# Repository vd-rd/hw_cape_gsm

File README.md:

## Description
Open hardware module for providing communications support via GPRS to embedded projects. The module can use any 2G network operating in the 850/900MHz or 1800/1900MHz spectrum. The modem features an audio link for voice calls and a TCP/IP stack for data transfer.

## Documentation

 Documentation for the module is available in the [docs folder](docs).
 
 Various resources used to design the module are available in the [resources folder](resources).

### Features
 * MicroSIM connector
 * 3.5mm jack with microphone
 * status LED indicator
 * two serial ports ( ATcommands on main serial port and support for daisy chaining a second UART device)
 * standard u.FL connector for antenna
 * standard ApolloIoT expansion header

### Resources
You can find all necesary information to build or evaluate the module here:
   - [View 3D board render](https://a360.co/2FHexOh)
   - [Fabrication files](https://github.com/vd-rd/hw_cape_gsm/releases)

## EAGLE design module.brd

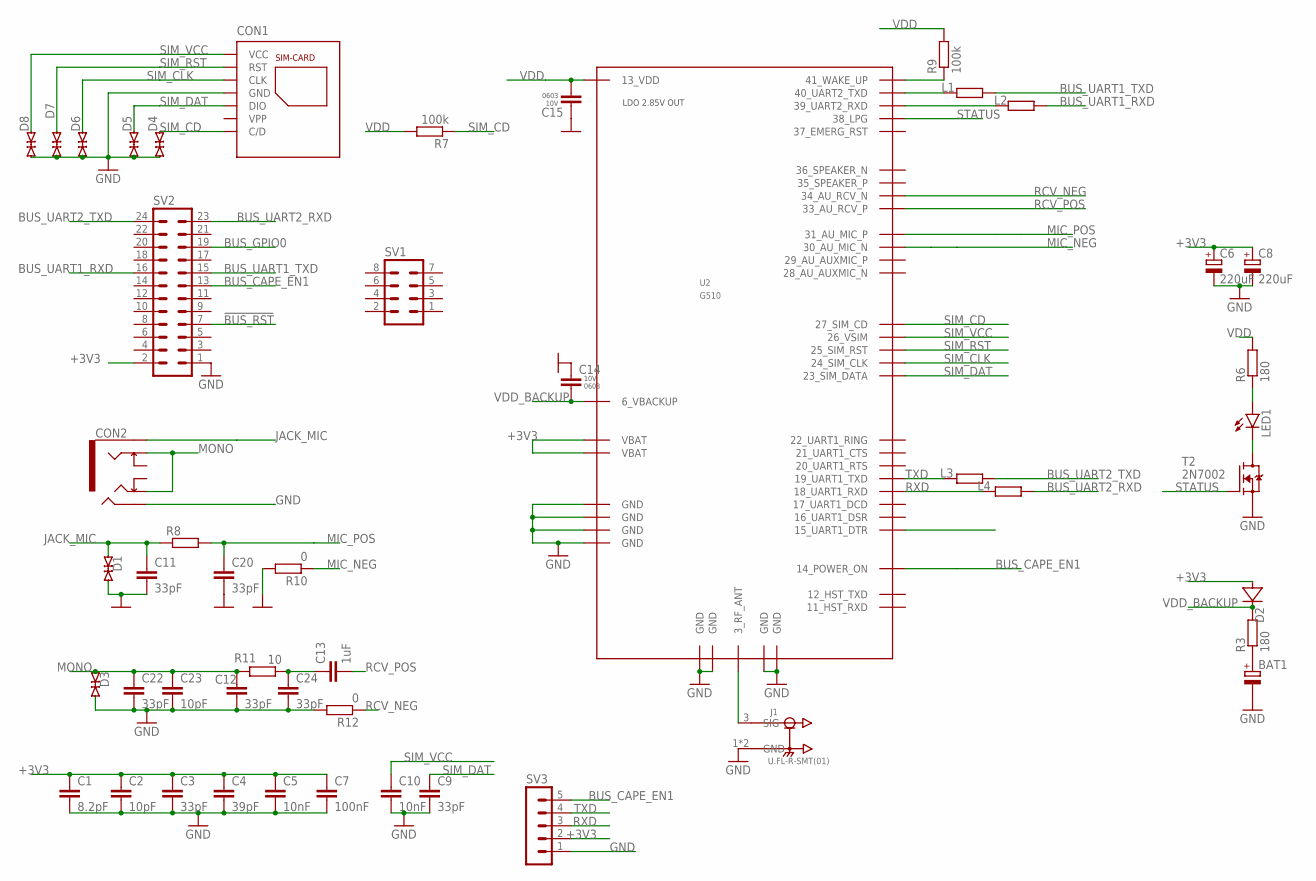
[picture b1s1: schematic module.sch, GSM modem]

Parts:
BAT1: DCK-3R3E224U-E; 621
C1: 8.2pF; C0402K
C2, C23: 10pF; C0402K
C3, C11, C12, C20, C22, C24: 33pF; C0402K
C4: 39pF; C0402K
C5, C10: 10nF; C0603
C6, C8: 220uF; SMC_C
C7: 100nF; C0603
C9: 33pF; C0603
C13: 1uF; C0402K
C14, C15: CAP-0603; C0603
CON1: 115Q-BCA0; 115Q
CON2: 1503-21; 150321
D1, D3, D4, D5, D6, D7, D8: ESD9B5.0ST5G; SOD1006X40
D2: 1N4148WS; SOD323
J1: U.FL-R-SMT(01); HRS_U.FL-R-SMT(01)
L1, L2, L3, L4: RES-0603; R0603
LED1: LEDCHIP-LED0603; CHIP-LED0603
R3, R6: 180; R0603
R7, R9: 100k; R0603
R8: R-EU_R0402; R0402
R10, R12: 0; R0402
R11: 10; R0402
SV1: MA04-2
SV2: MA12-2
SV3: MA05-1
T2: 2N7002; SOT95P240X110-3
U2: G510

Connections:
!BUS_RST: SV2.7
+3V3: C1.1, C2.1, C3.1, C4.1, C5.1, C6.+, C7.1, C8.+, D2.A, SV2.2, SV3.2, U2.9_VBAT (VBAT), U2.10_VBAT (VBAT)
BUS_CAPE_EN1: SV2.13, SV3.5, U2.14_POWER_ON
BUS_GPIO0: SV2.19
BUS_UART1_RXD: L2.2, SV2.16
BUS_UART1_TXD: L1.2, SV2.15
BUS_UART2_RXD: L4.2, SV2.23
BUS_UART2_TXD: L3.2, SV2.24
GND: BAT1.-, C1.2, C2.2, C3.2, C4.2, C5.2, C6.-, C7.2, C8.-, C9.2, C10.2, C11.2, C12.2, C14.1, C15.1, C20.2, C22.2, C23.2, C24.2, CON1.GND1 (GND), CON1.GND2 (GND), CON1.GND3 (GND), CON1.GND4 (GND), CON1.P5 (GND), CON2.2, D1.2 (C), D3.2 (C), D4.1 (A), D5.1 (A), D6.1 (A), D7.1 (A), D8.1 (A), J1.1 (GND), J1.2 (GND), R10.2, R12.2, SV2.1, SV3.1, T2.2 (S), U2.1_GND (GND), U2.2_GND (GND), U2.4_GND (GND), U2.5_GND (GND), U2.7_GND (GND), U2.8_GND (GND), U2.32_GND (GND), U2.42_GND (GND)
JACK_MIC: C11.1, CON2.1, D1.1 (A), R8.1
MIC_NEG: R10.1, U2.30_AU_MIC_N
MIC_POS: C20.1, R8.2, U2.31_AU_MIC_P
MONO: C12.1, C22.1, C23.1, CON2.3, CON2.5, D3.1 (A), R11.2
unnamed: BAT1.+, R3.1
unnamed: C13.1, C24.1, R11.1
unnamed: J1.3 (SIG), U2.3_RF_ANT
unnamed: LED1.C, T2.3 (D)
unnamed: R9.1, U2.41_WAKE_UP
unnamed: LED1.A, R6.1
RCV_NEG: R12.1, U2.34_AU_RCV_N
RCV_POS: C13.2, U2.33_AU_RCV_P
RXD: L4.1, SV3.3, U2.18_UART1_RXD
SIM_CD: CON1.CD (C/D), D4.2 (C), R7.1, U2.27_SIM_CD
SIM_CLK: CON1.P3 (CLK), D6.2 (C), U2.24_SIM_CLK
SIM_DAT: C9.1, CON1.P7 (DIO), D5.2 (C), U2.23_SIM_DATA
SIM_RST: CON1.P2 (RST), D7.2 (C), U2.25_SIM_RST
SIM_VCC: C10.1, CON1.P1 (VCC), D8.2 (C), U2.26_VSIM
STATUS: T2.1 (G), U2.38_LPG
TXD: L3.1, SV3.4, U2.19_UART1_TXD
UART_RXD: L2.1, U2.39_UART2_RXD
UART_TXD: L1.1, U2.40_UART2_TXD
VDD: C15.2, R6.2, R7.2, R9.2, U2.13_VDD
VDD_BACKUP: C14.2, D2.K (C), R3.2, U2.6_VBACKUP

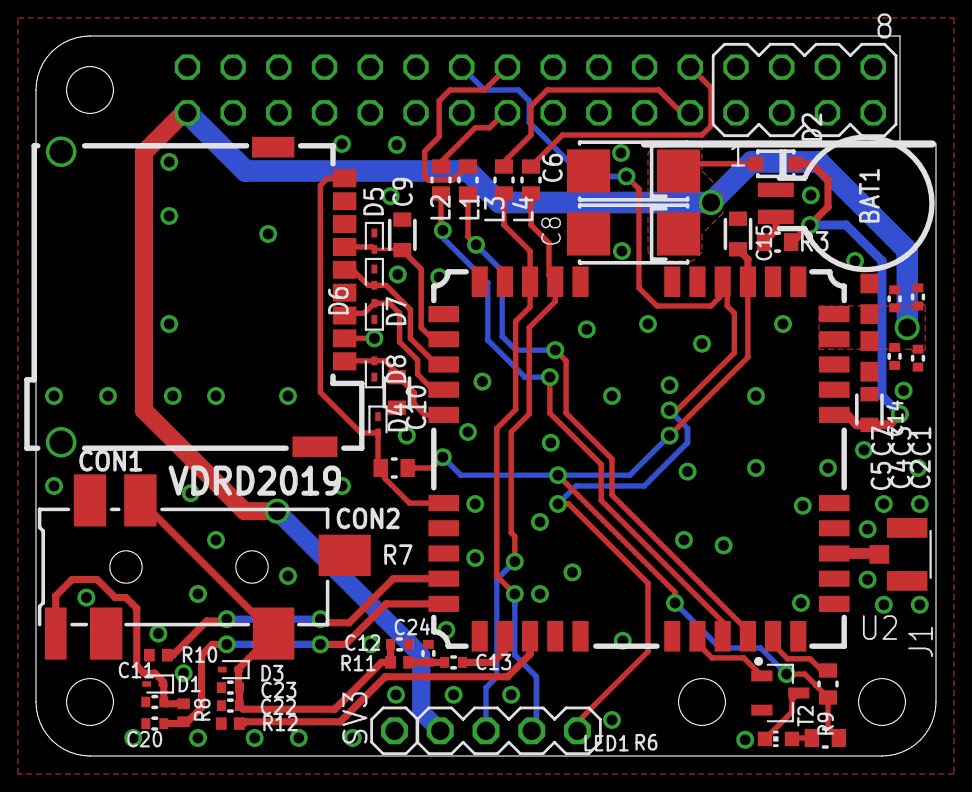
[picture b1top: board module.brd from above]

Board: 2 copper layers, 50.0 x 40.0 mm, 49 parts (1 on the bottom side), 31 nets.

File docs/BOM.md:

## Revision 1.0 BOM

[Complete BOM and example parts](https://docs.google.com/spreadsheets/d/138vCS7z_F9O98r_FUHqW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

| Qty | Parts | Package | Value | Description | Part id |
| ------ | ------ | ------ |------ | ------ | ------ |
| 1 | CON1 |	| |	Connector: for cards; Micro SIM; push-push; SMT; PIN: 8	| 115Q-BCA0 |
| 2	| C14, C15 |	0603 | 100nF |	Capacitor: ceramic; MLCC; 100nF; 16V; X7R; ±10%; SMD; 0603 |	CL10B104KO8NNNC |
| 7	| D1, D3, D4, D5, D6, D7, D8 |	SOD923 | | Diode: transil; 300mW; 7.8V; 15A; bidirectional; SOD923 |	ESD9B5.0ST5G |
| 4	| L1, L2, L3, L4 |	0603 | |		Ferrite: bead; Imp.@ 100MHz: 120Ω; Mounting: SMD; 0.2A; Case: 0603 |	BLM18AG121SN1D |
|2	| R7, R9 |	0603 |	100k |	Resistor: thick film; SMD; 0603; 100kΩ; 0.1W; ±5%; -55÷155°C |	SMD0603-100K |
| 1	| C7 |	 0603 |	100nF |	Capacitor: ceramic; MLCC; 100nF; 16V; X7R; ±10%; SMD; 0603 |	CL10B104KO8NNNC |
| 2	| C5, C10 |	 0603 |	10nF |	Capacitor: ceramic; MLCC; 10nF; 50V; X7R; ±10%; SMD; 0603 |	VJ0603Y103KXAPW1BC |
| 1	| C2 |	0402 |	10pF |	Capacitor: ceramic; MLCC; 10pF; 50V; C0G; ±0.5pF; SMD; 0402 |	0402N100D500CT |
| 2	| C6, C8 |	SMC_C |	220uF |	Capacitor: tantalum; 220uF; 4VDC; SMD; Case: C; 2312; ±10%; -55÷125°C	| TAJC227K004R |
| 1	| C3 |	0402 |	33pF |	Capacitor: ceramic; 33pF; 50V; C0G; ±5%; SMD; 0402; Series: GRM	| GRM1555C1H330JA01D |
| 1	| C4 |	0402 |	39pF |	Capacitor: ceramic; 39pF; 50V; C0G; ±5%; SMD; 0402; Series: GRM	| GRM1555C1H390JA01D |
| 1	| C1 | 0402 |	8.2pF	| Capacitor: ceramic; 8.2pF; 50V; C0G; ±0.25pF; SMD; 0402; Series: GRM |	GRM1555C1H8R2CA01D |
| 1	| U2 | | | Module: GSM; GPRS; 2G; D: 85.6kbps; Audio x2,GPIO,UART x2; -40÷85°C |	G510-Q50-00 |
| 1	| J1 | | | Connector: U.FL (IPX/AMC); socket; 50Ω; SMT; male; 1.25mm |	MX-73412-0114 |
| 1 |	LED1 |	CHIP-LED0603 | | LED	
| 1	| D2 |	SOD323 | | 1N4148			
| 1 |	BAT1 |	621 | |	DCK-3R3E404T-E
| 1	| T2 |	SOT23 | |	2N7002		
| 2	| R3, R6 |	0603|	180 | 
| 1 |	CON2 |				
| 1 |	R8 |	R0402 | |	RESISTOR, European symbol	 |
| 2 |	R10, R12 | 	R0402 | 0 |	RESISTOR, European symbol	|
| 1 |	R11 |	R0402 |	10 |	RESISTOR, European symbol	|
| 2	| C23	| C0402K |	10pF |		
| 1	| C13 |	C0402K |	1uF |		
| 7	| C3, C9, C11, C12, C20, C22, C24 |	C0402K |	33pF |

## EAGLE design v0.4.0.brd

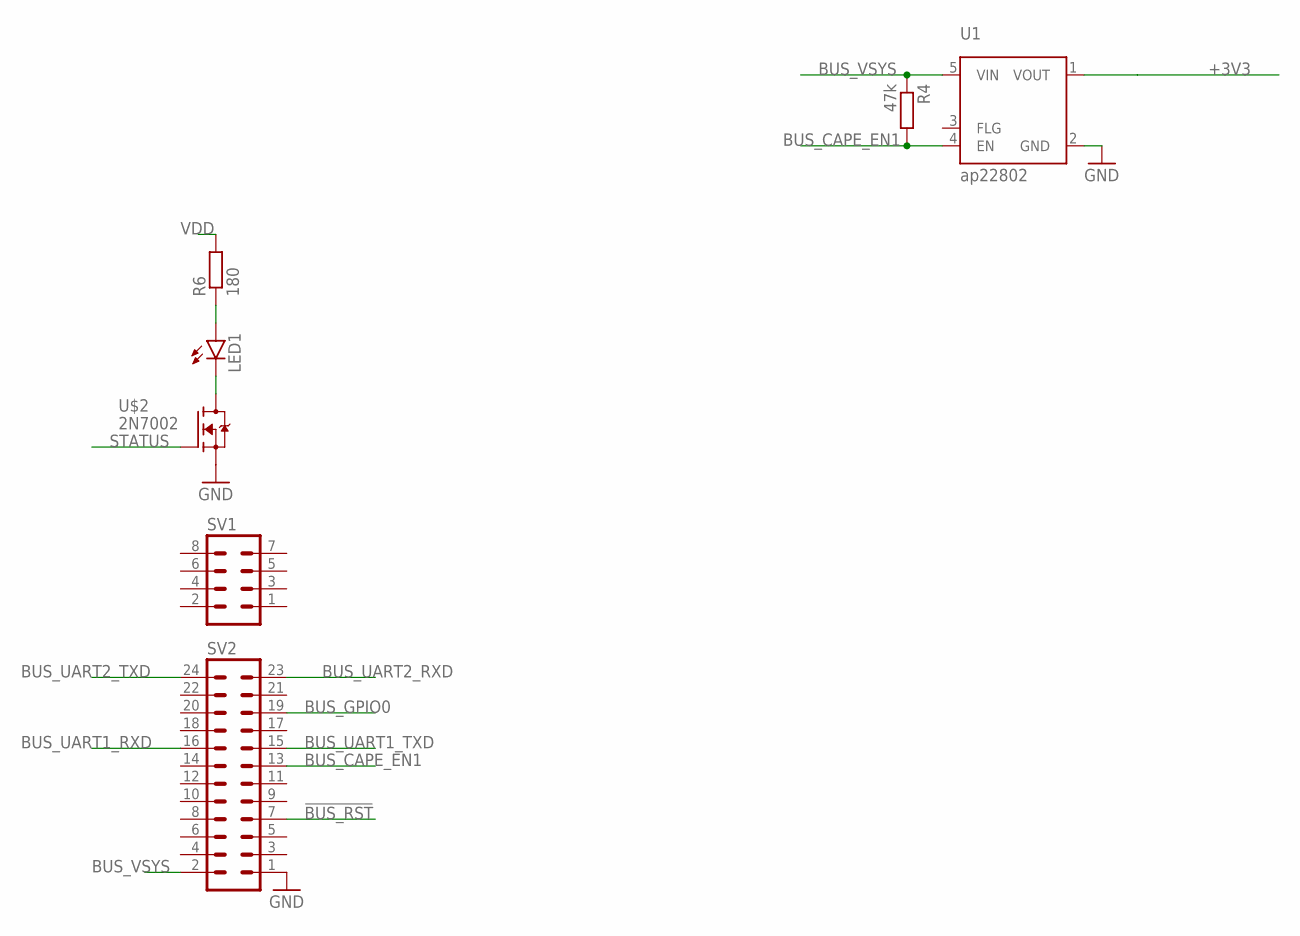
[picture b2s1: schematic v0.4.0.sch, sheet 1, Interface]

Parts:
LED1: LEDCHIP-LED0603; CHIP-LED0603
R4: 47k; R0402
R6: 180; R0402
SV1: MA04-2
SV2: MA12-2
U1: ap22802; SOT25
U$2: 2N7002; SOT95P240X110-3

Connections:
!BUS_RST: SV2.7; also elsewhere on the board
+3V3: U1.1 (VOUT); also elsewhere on the board
BUS_CAPE_EN1: R4.2, SV2.13, U1.4 (EN); also elsewhere on the board
BUS_GPIO0: SV2.19; also elsewhere on the board
BUS_UART1_RXD: SV2.16; also elsewhere on the board
BUS_UART1_TXD: SV2.15; also elsewhere on the board
BUS_UART2_RXD: SV2.23; also elsewhere on the board
BUS_UART2_TXD: SV2.24; also elsewhere on the board
BUS_VSYS: R4.1, SV2.2, U1.5 (VIN)
GND: SV2.1, U1.2 (GND), U$2.2 (S); also elsewhere on the board
unnamed: LED1.C, U$2.3 (D)
unnamed: LED1.A, R6.1
STATUS: U$2.1 (G); also elsewhere on the board
VDD: R6.2; also elsewhere on the board

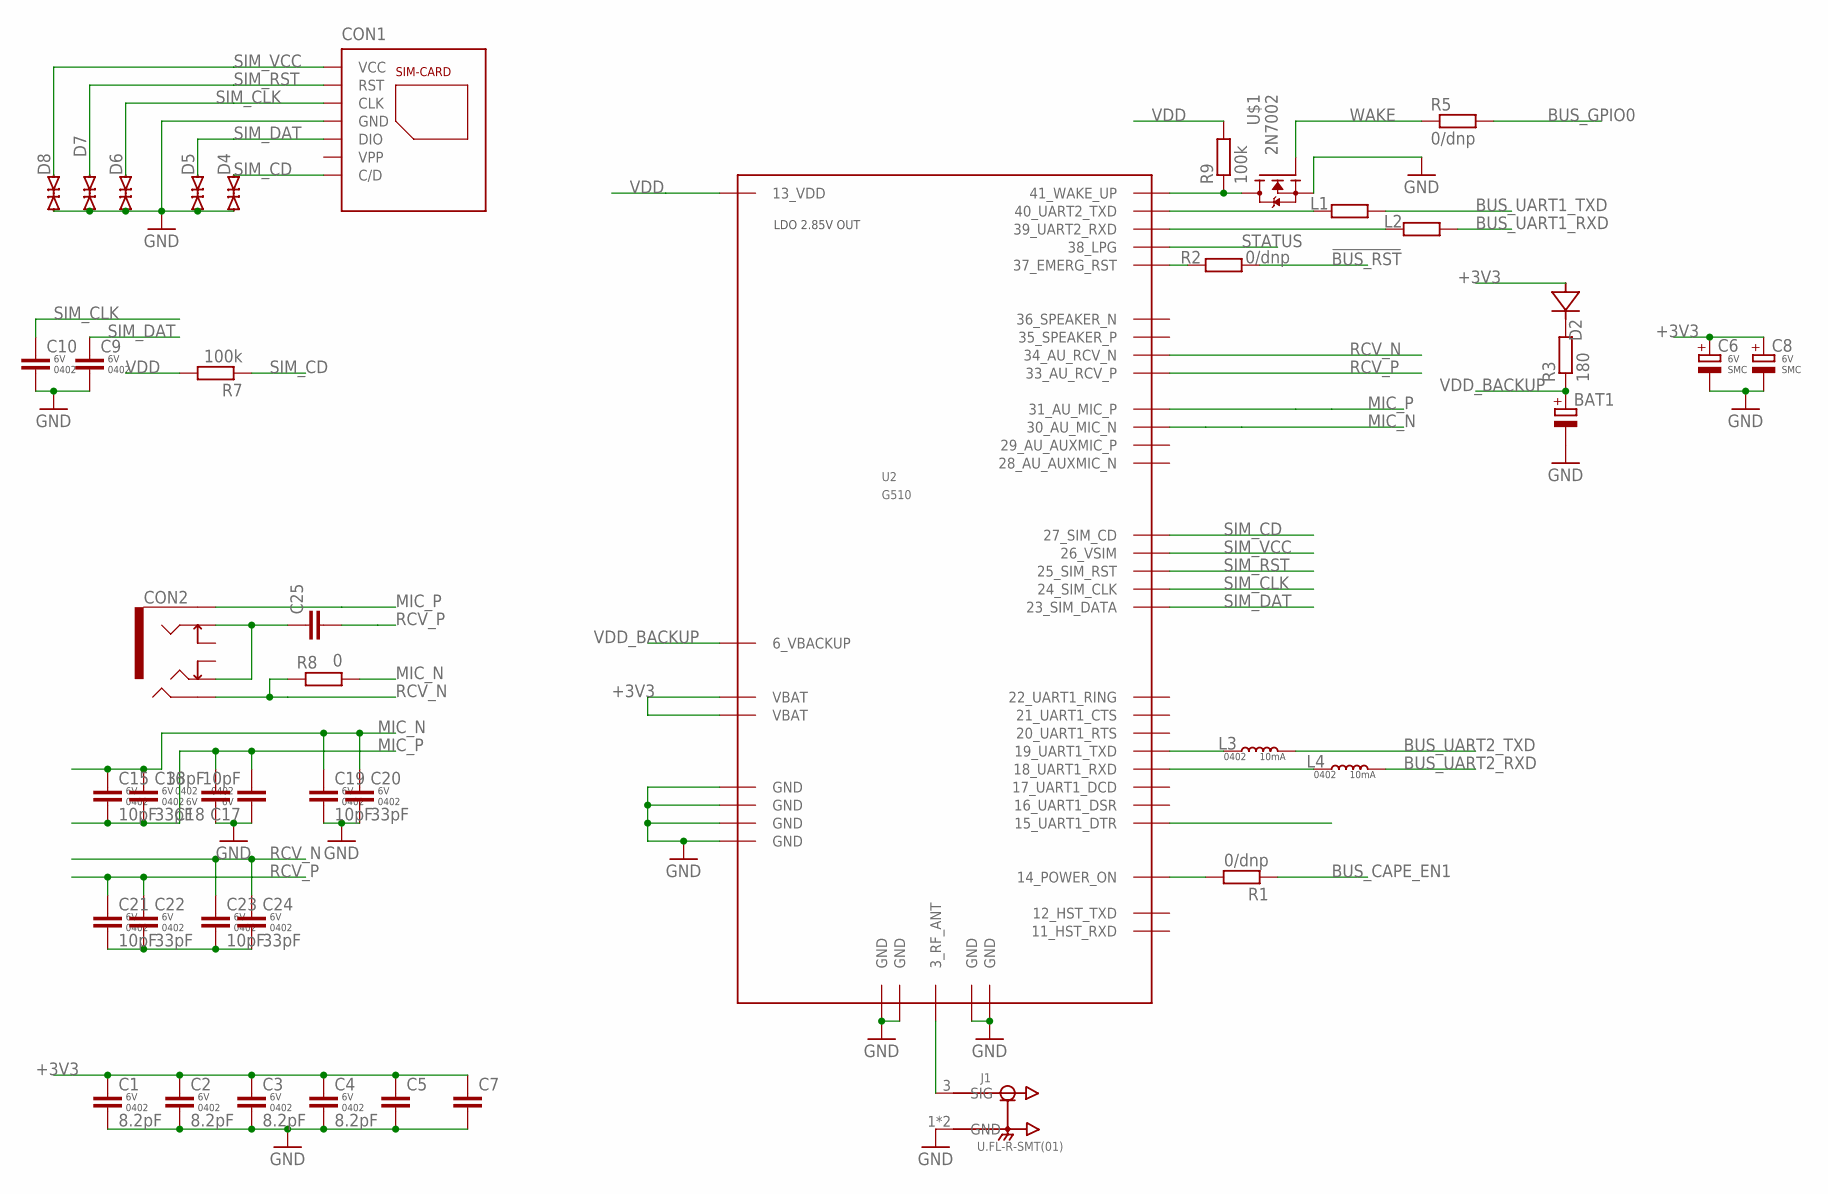
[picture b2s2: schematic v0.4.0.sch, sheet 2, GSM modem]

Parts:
BAT1: DCK-3R3E224U-E; 621
C1, C2, C3, C4: 8.2pF; C0402K
C5, C7, C25: C-EUC0603; C0603
C6, C8: CAP-POL-SMC; SMC_C
C9, C10: CAP-0402; C0402K
C15, C17, C19, C21, C23: 10pF; C0402K
C16, C18, C20, C22, C24: 33pF; C0402K
CON1: 115Q-BCA0; 115Q
CON2: 1503-21; 150321
D2: 1N4148WS; SOD323
D4, D5, D6, D7, D8: ESD9B5.0ST5G; SOD1006X40
J1: U.FL-R-SMT(01); HRS_U.FL-R-SMT(01)
L1, L2: R-EU_R0402; R0402
L3, L4: IND-0402; L0402
R1, R2, R5: 0/dnp; R0402
R3: 180; R0402
R7, R9: 100k; R0402
R8: 0; R0402
U2: G510
U$1: 2N7002; SOT95P240X110-3

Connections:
!BUS_RST: R2.2; also elsewhere on the board
+3V3: C1.1, C2.1, C3.1, C4.1, C5.1, C6.+, C7.1, C8.+, D2.A, U2.9_VBAT (VBAT), U2.10_VBAT (VBAT); also elsewhere on the board
BUS_CAPE_EN1: R1.1; also elsewhere on the board
BUS_GPIO0: R5.2; also elsewhere on the board
BUS_UART1_RXD: L2.2; also elsewhere on the board
BUS_UART1_TXD: L1.2; also elsewhere on the board
BUS_UART2_RXD: L4.2; also elsewhere on the board
BUS_UART2_TXD: L3.2; also elsewhere on the board
GND: BAT1.-, C1.2, C2.2, C3.2, C4.2, C5.2, C6.-, C7.2, C8.-, C9.2, C10.2, C17.1, C18.1, C19.2, C20.2, CON1.GND1 (GND), CON1.GND2 (GND), CON1.GND3 (GND), CON1.GND4 (GND), CON1.P5 (GND), D4.1 (A), D5.1 (A), D6.1 (A), D7.1 (A), D8.1 (A), J1.1 (GND), J1.2 (GND), U2.1_GND (GND), U2.2_GND (GND), U2.4_GND (GND), U2.5_GND (GND), U2.7_GND (GND), U2.8_GND (GND), U2.32_GND (GND), U2.42_GND (GND), U$1.2 (S); also elsewhere on the board
MIC_N: C15.1, C16.1, C19.1, C20.1, R8.2, U2.30_AU_MIC_N
MIC_P: C15.2, C16.2, C17.2, C18.2, CON2.1, U2.31_AU_MIC_P
unnamed: C21.2, C22.2, C23.2, C24.2
unnamed: L3.1, U2.19_UART1_TXD
unnamed: J1.3 (SIG), U2.3_RF_ANT
unnamed: R9.1, U2.41_WAKE_UP, U$1.3 (D)
unnamed: L4.1, U2.18_UART1_RXD
unnamed: R2.1, U2.37_EMERG_RST
unnamed: L1.1, U2.40_UART2_TXD
unnamed: L2.1, U2.39_UART2_RXD
unnamed: R1.2, U2.14_POWER_ON
unnamed: D2.K (C), R3.2
unnamed: C25.1, CON2.3, CON2.5
RCV_N: C23.1, C24.1, CON2.2, R8.1, U2.34_AU_RCV_N
RCV_P: C21.1, C22.1, C25.2, U2.33_AU_RCV_P
SIM_CD: CON1.CD (C/D), D4.2 (C), R7.1, U2.27_SIM_CD
SIM_CLK: C10.1, CON1.P3 (CLK), D6.2 (C), U2.24_SIM_CLK
SIM_DAT: C9.1, CON1.P7 (DIO), D5.2 (C), U2.23_SIM_DATA
SIM_RST: CON1.P2 (RST), D7.2 (C), U2.25_SIM_RST
SIM_VCC: CON1.P1 (VCC), D8.2 (C), U2.26_VSIM
STATUS: U2.38_LPG; also elsewhere on the board
VDD: R7.2, R9.2, U2.13_VDD; also elsewhere on the board
VDD_BACKUP: BAT1.+, R3.1, U2.6_VBACKUP
WAKE: R5.1, U$1.1 (G)

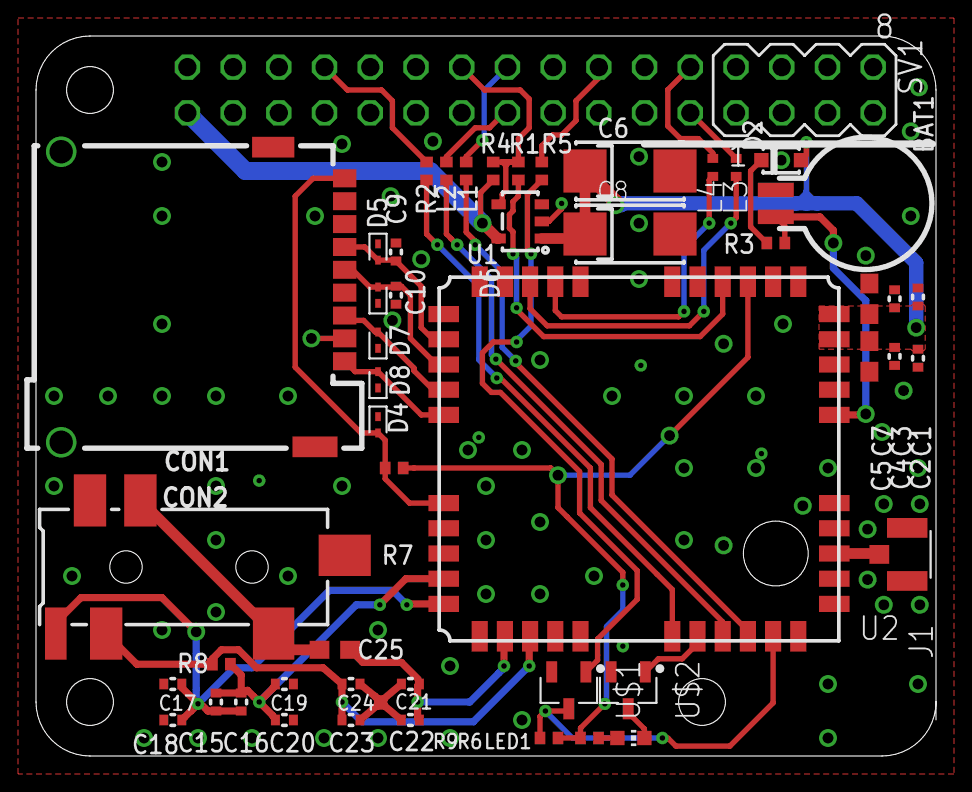
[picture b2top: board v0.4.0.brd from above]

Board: 2 copper layers, 50.0 x 40.0 mm, 51 parts (1 on the bottom side), 36 nets.

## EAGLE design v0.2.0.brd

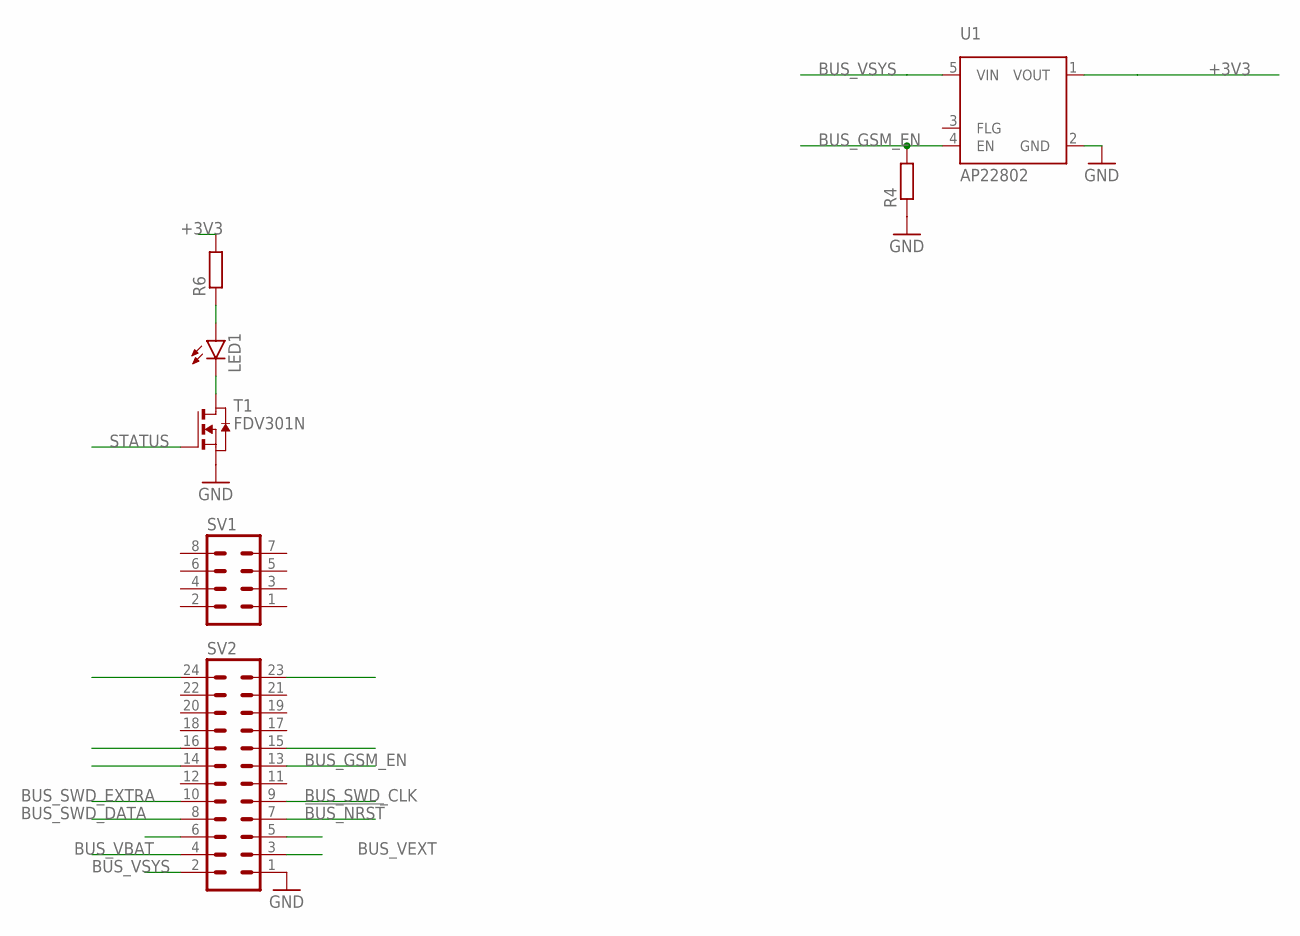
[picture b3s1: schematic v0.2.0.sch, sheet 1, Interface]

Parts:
LED1: LEDCHIP-LED0603; CHIP-LED0603
R4, R6: R-EU_R0402; R0402
SV1: MA04-2
SV2: MA12-2
T1: FDV301N; SOT-23
U1: AP22802; SOT25

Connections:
!BUS_NRST: SV2.7
+3V3: R6.2, U1.1 (VOUT); also elsewhere on the board
BUS_GSM_EN: R4.2, SV2.13, U1.4 (EN)
BUS_SWD_CLK: SV2.9
BUS_SWD_DATA: SV2.8
BUS_SWD_EXTRA: SV2.10
BUS_VBAT: SV2.4
BUS_VEXT: SV2.3
BUS_VSYS: SV2.2, U1.5 (VIN)
GND: R4.1, SV2.1, T1.2 (S), U1.2 (GND); also elsewhere on the board
unnamed: LED1.C, T1.1 (D)
unnamed: LED1.A, R6.1
STATUS: T1.3 (G); also elsewhere on the board

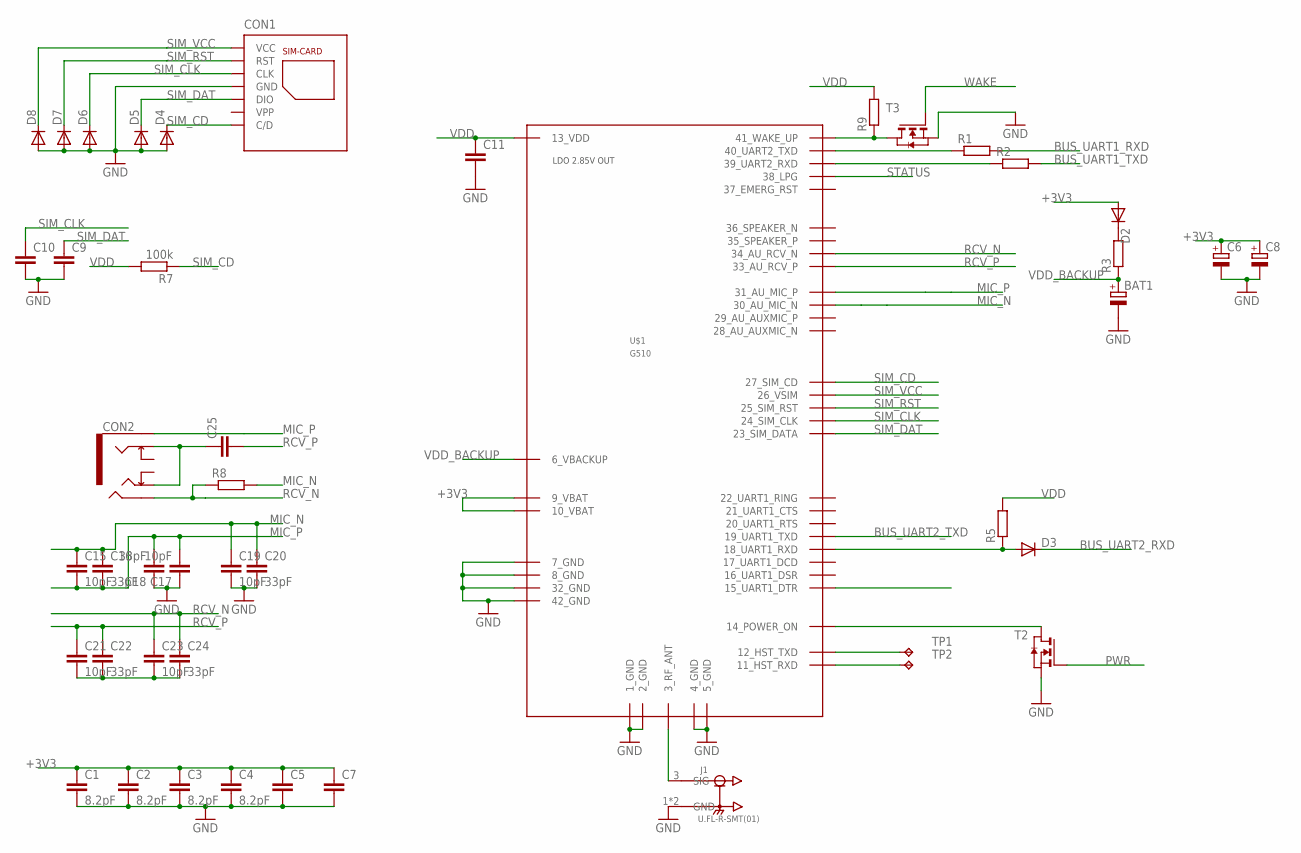
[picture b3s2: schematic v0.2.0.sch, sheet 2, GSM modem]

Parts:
BAT1: DCK-3R3E224U-E; 621
C1, C2, C3, C4: 8.2pF; C0402
C5, C7, C25: C-EUC0603; C0603
C6, C8: CPOL-EUSMCC; SMC_C
C9, C10, C11: C-EUC0402; C0402
C15, C17, C19, C21, C23: 10pF; C0402
C16, C18, C20, C22, C24: 33pF; C0402
CON1: 115Q-BCA0; 115Q
CON2: 1503-21; 150321
D2, D3, D4, D5, D6, D7, D8: DIODE-SOD323-R; SOD323-R
J1: U.FL-R-SMT(01); HRS_U.FL-R-SMT(01)
R1, R2, R3, R5, R8, R9: R-EU_R0402; R0402
R7: 100k; R0402
T2, T3: NMOSSOT23; SOT-23
TP1, TP2: TPB1,27; B1,27
U$1: G510

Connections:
+3V3: C1.1, C2.1, C3.1, C4.1, C5.1, C6.+, C7.1, C8.+, D2.A, U$1.9_VBAT, U$1.10_VBAT; also elsewhere on the board
BUS_UART1_RXD: R1.2
BUS_UART1_TXD: R2.2
BUS_UART2_RXD: D3.C
BUS_UART2_TXD: U$1.19_UART1_TXD
GND: BAT1.-, C1.2, C2.2, C3.2, C4.2, C5.2, C6.-, C7.2, C8.-, C9.2, C10.2, C11.2, C17.1, C18.1, C19.2, C20.2, CON1.GND1 (GND), CON1.GND2 (GND), CON1.GND3 (GND), CON1.GND4 (GND), CON1.P5 (GND), D4.A, D5.A, D6.A, D7.A, D8.A, J1.1 (GND), J1.2 (GND), T2.2 (S), T3.2 (S), U$1.1_GND, U$1.2_GND, U$1.4_GND, U$1.5_GND, U$1.7_GND, U$1.8_GND, U$1.32_GND, U$1.42_GND; also elsewhere on the board
MIC_N: C15.1, C16.1, C19.1, C20.1, R8.2, U$1.30_AU_MIC_N
MIC_P: C15.2, C16.2, C17.2, C18.2, CON2.1, U$1.31_AU_MIC_P
unnamed: C21.2, C22.2, C23.2, C24.2
unnamed: J1.3 (SIG), U$1.3_RF_ANT
unnamed: R9.1, T3.1 (D), U$1.41_WAKE_UP
unnamed: D3.A, R5.1, U$1.18_UART1_RXD
unnamed: R1.1, U$1.40_UART2_TXD
unnamed: R2.1, U$1.39_UART2_RXD
unnamed: T2.1 (D), U$1.14_POWER_ON
unnamed: TP1.TP, U$1.12_HST_TXD
unnamed: TP2.TP, U$1.11_HSTRXD (11_HST_RXD)
unnamed: D2.C, R3.2
unnamed: C25.1, CON2.3, CON2.5
PWR: T2.3 (G)
RCV_N: C23.1, C24.1, CON2.2, R8.1, U$1.34_AU_RCV_N
RCV_P: C21.1, C22.1, C25.2, U$1.33_AU_RCV_P
SIM_CD: CON1.CD (C/D), D4.C, R7.1, U$1.27_SIM_CD
SIM_CLK: C10.1, CON1.P3 (CLK), D6.C, U$1.24_SIM_CLK
SIM_DAT: C9.1, CON1.P7 (DIO), D5.C, U$1.23_SIM_DATA
SIM_RST: CON1.P2 (RST), D7.C, U$1.25_SIM_RST
SIM_VCC: CON1.P1 (VCC), D8.C, U$1.26_VSIM
STATUS: U$1.38_LPG; also elsewhere on the board
VDD: C11.1, R5.2, R7.2, R9.2, U$1.13_VDD
VDD_BACKUP: BAT1.+, R3.1, U$1.6_VBACKUP
WAKE: T3.3 (G)

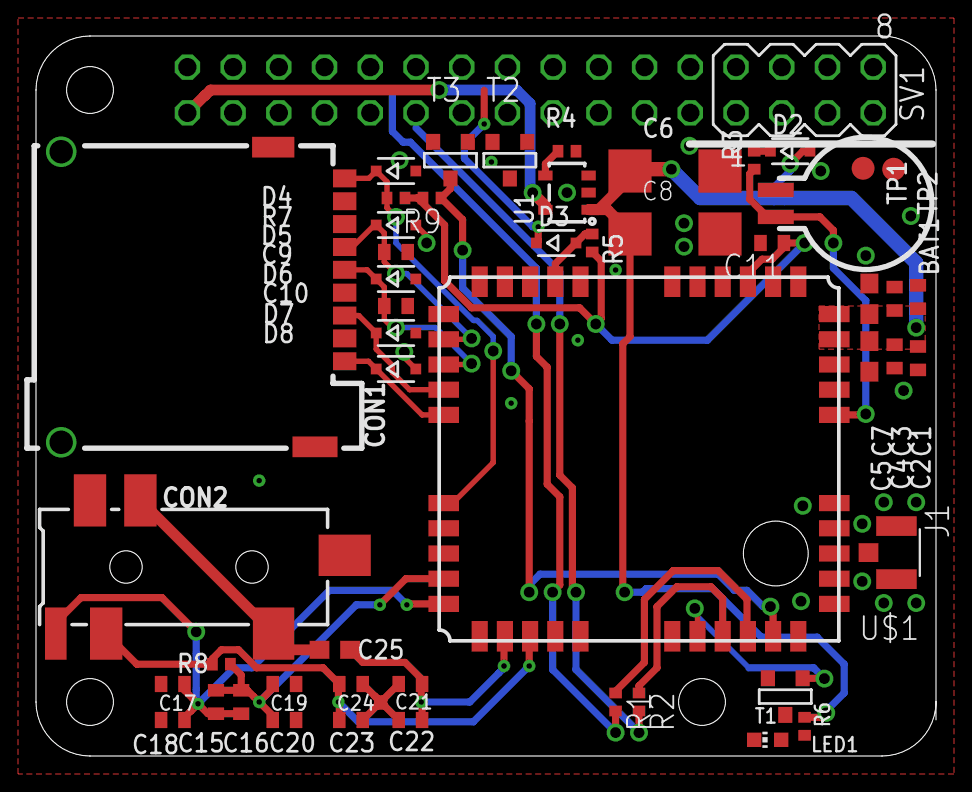
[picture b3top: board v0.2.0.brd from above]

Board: 2 copper layers, 50.0 x 40.0 mm, 52 parts (1 on the bottom side), 29 nets.

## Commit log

2018-12-13 board bringup and floorplan
2018-12-14 added support components
2018-12-14 added audio filtering
2018-12-21 corrected sim connector
2018-12-21 removed extra caps
2018-12-21 routed most nets
2018-12-21 routed new nets
2018-12-21 floorplan optimisations
2018-12-21 added vias for ground emi
2018-12-21 naming fixes
2018-12-21 minor fixes'
2019-01-07 bench tested
2019-01-08 improved ground emi
2019-01-20 updated footprints
2019-01-20 improved audio interface
2019-01-20 cosmetic fixes
2019-01-22 added jack switch docs
2019-01-23 added output files
2019-03-12 space optimisation
2019-05-02 project: structure update
2019-05-02 project: old files cleanup
2019-05-20 board: add pinout and markings
2019-05-20 project: added pictures
2019-05-20 project: fixed small typos
2019-05-20 Board: add breakout header
2019-05-20 board: added mechanical data
2019-05-21 project: moved resources
2019-05-21 project: added board overview
2019-05-21 board: added breakout header
2019-05-21 project: prepared v1.1.0 rev
